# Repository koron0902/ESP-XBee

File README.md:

## OverView
ESP-WROOM-02をXBeeと同じコネクタで使えるようにするやつ

## Function
- USB Power Supply(+5V) 
  - USBでのバスパワー駆動に対応します．
- PC Connection 
  - USB-Serial変換チップを搭載しているのでファームウェアアップデートが容易です．
  - また，通信路に介入することができます．(WiFiで送信したデータをシリアルでループバック可能)
  - PC --> (XBee-RX == ESP-U0RX), (XBee-TX == ESP-U0TX) --> PC
- リセットボタン
  - EN端子が制御元と接続されていても，依存しないリセットを発行することができます．

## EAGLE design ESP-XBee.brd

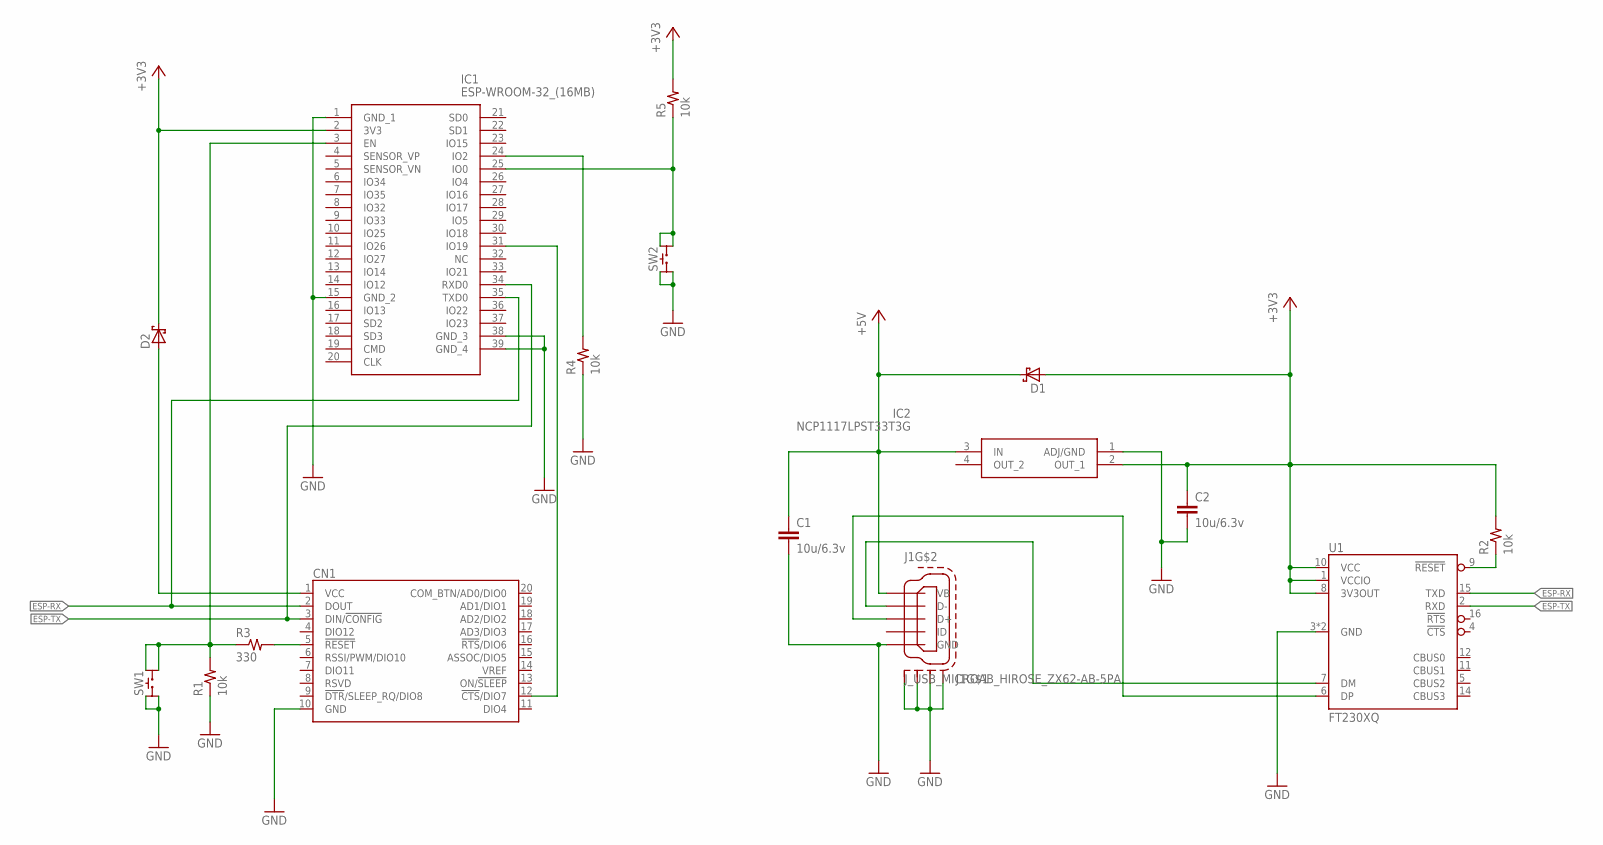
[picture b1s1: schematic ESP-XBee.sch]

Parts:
C1, C2: 10u/6.3v; 1005
CN1: XBEE-TH
D1, D2: SBD-SOD523; SOD523
IC1: ESP-WROOM-32_(16MB); ESP32SOLO1
IC2: NCP1117LPST33T3G; SOT230P700X180-4N
J1: J_USB_MICROAB_HIROSE_ZX62-AB-5PA
R1, R2, R4, R5: 10k; 1005
R3: 330; 1005
SW1, SW2: SKRP
U1: FT230XQ; QFN16-0.65-NOPAD

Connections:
+3V3: C2.1, D1.A, D2.K, IC1.2 (3V3), IC2.2 (OUT_1), R2.2, R5.2, U1.1 (VCCIO), U1.8 (3V3OUT), U1.10 (VCC)
+5V: C1.1, D1.K, IC2.3 (IN), J1.P$1 (VB)
ESP-RX: CN1.2 (DOUT), IC1.35 (TXD0), U1.15 (TXD)
ESP-TX: CN1.3 (DIN/!CONFIG), IC1.34 (RXD0), U1.2 (RXD)
GND: C1.2, C2.2, CN1.10 (GND), IC1.1 (GND_1), IC1.15 (GND_2), IC1.38 (GND_3), IC1.39 (GND_4), IC2.1 (ADJ/GND), J1.P$5 (GND), J1.SHIELD1 (S1), J1.SHIELD2 (S2), J1.SHIELD3 (S3), J1.SHIELD4 (S4), R1.1, R4.1, SW1.A1, SW1.A2, SW2.A1, SW2.A2, U1.3 (GND), U1.13 (GND)
unnamed: CN1.1 (VCC), D2.A
unnamed: IC1.3 (EN), R1.2, R3.1, SW1.B1, SW1.B2
unnamed: J1.P$3 (D+), U1.6 (DP)
unnamed: CN1.12 (!CTS!/DIO7), IC1.31 (IO19)
unnamed: J1.P$2 (D-), U1.7 (DM)
unnamed: R2.1, U1.9 (!RESET)
unnamed: CN1.5 (!RESET), R3.2
unnamed: IC1.24 (IO2), R4.2
unnamed: IC1.25 (IO0), R5.1, SW2.B1, SW2.B2

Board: 2 copper layers, 16 parts (0 on the bottom side), 14 nets, no tracks yet.

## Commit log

2019-12-06 READMEとlbrのパス
